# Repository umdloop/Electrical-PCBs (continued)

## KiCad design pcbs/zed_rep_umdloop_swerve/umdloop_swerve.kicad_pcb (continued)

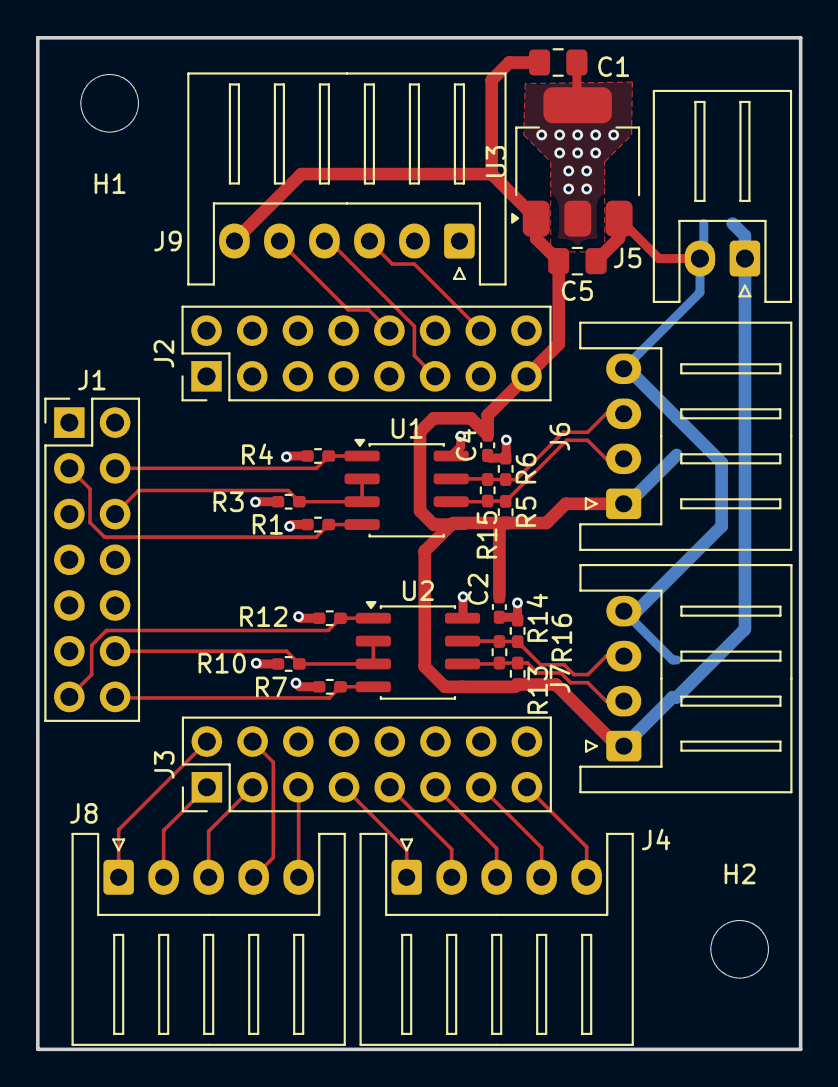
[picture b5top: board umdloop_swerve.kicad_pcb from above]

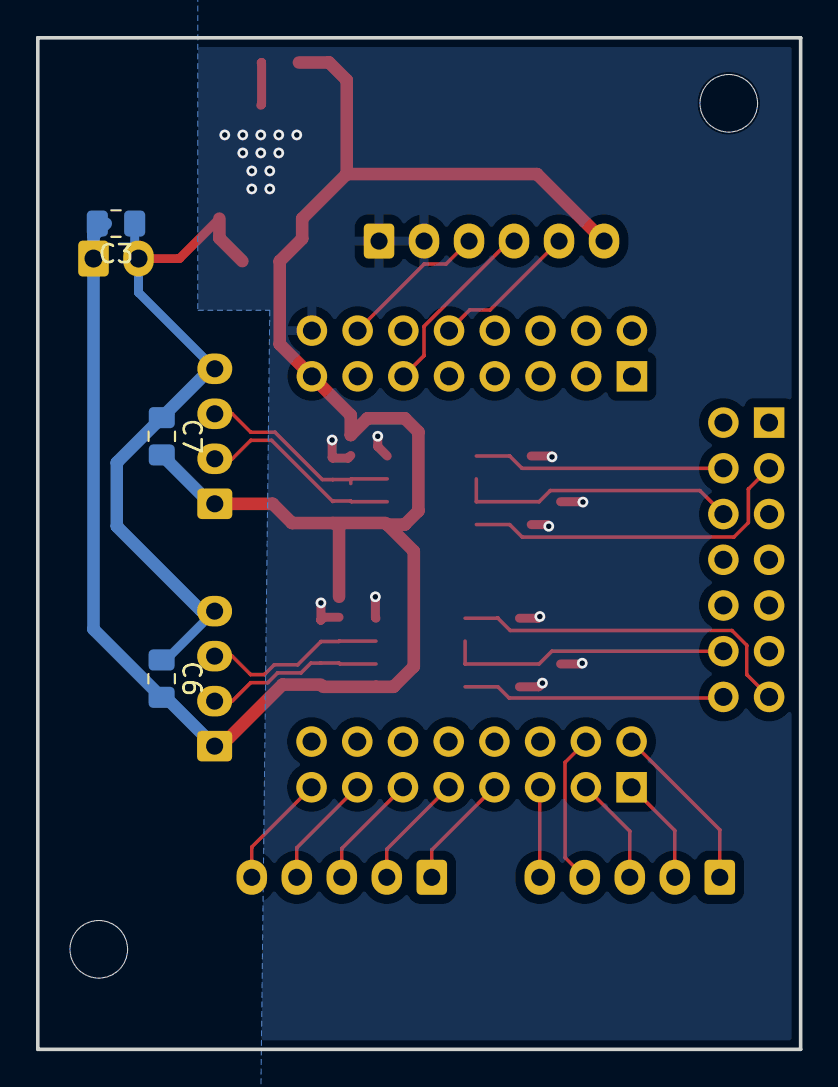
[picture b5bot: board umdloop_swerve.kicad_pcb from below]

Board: 2 copper layers, 42.4 x 56.2 mm, 33 parts (3 on the bottom side), 26 nets.
